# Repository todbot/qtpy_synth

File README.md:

# qtpy_synth

A simple [QTPy RP2040](https://learn.adafruit.com/adafruit-qt-py-2040/overview)-based
synth to experiment with [`synthio`](https://github.com/todbot/circuitpython-synthio-tricks).

### Features
 - Mono audio output circuit, converting PWM to audio, as per [RP2040 design guidelines](https://datasheets.raspberrypi.com/rp2040/hardware-design-with-rp2040.pdf#page=24)
 - Optoisolated MIDI Input via [MIDI TRS-A 3.5mm jack](https://www.perfectcircuit.com/make-noise-0-coast-midi-cable.html)
 - Two pots for controlling parameters
 - One switch for controlling parameters
 - Four capsense touch buttons for synth triggering
 - USB MIDI in/out of course too

### Software
Some programs written specifically for this board:

- [hwtest](./circuitpython/hwtest/code.py) - test out the hardware with a simple synth

- [simpletouchsynth](./circuitpython/simpletouchsynth) - play with filters using touch sensors. Uses intial cut at a "qtpy_synth" hardware library.

- [dronesynth](./circuitpython/dronesynth) - 8-oscillator drone synth

- [wavesynth](./circuitpython/wavesynth) - larger general two-osc synth that can also do wave-mixing and wavetables. Has many rough edges but can sound great!
  - early video demo:
  
    ]
  - another video demo:
  
    ]

#### See also:
- https://github.com/todbot/circuitpython-synthio-tricks
  - Contains [many other synthio examples](https://github.com/todbot/circuitpython-synthio-tricks/tree/main/examples) that can work with this synth with minimal changes

### Building it

The [Tindie version is a partially-assembled PCB](https://www.tindie.com/products/todbot/qtpy_synth/). 

The completely assembled SMD sections of the board are:

* audio output circuit
* TRS MIDI input circuit

The parts you need to add are:

* [QTPy RP2040](https://www.adafruit.com/product/4900)
* 0.91" [I2C OLED display](https://amzn.to/3KDmy73) (w/ pins in Gnd/Vcc/SCL/SDA order)
* Two 10k potentiometers, 9mm  ([example pots](https://amzn.to/3DYYJm5)) and [knobs](https://amzn.to/3QAkSyR)
* One tact switch, 6mm ([example switch](https://amzn.to/47nJaSN))
* Headers and sockets to mount QTPy & display, to taste
  * [This male & female header kit looks pretty good](https://amzn.to/3qqbtiO),
    as I prefer to put female headers on the PCB and male headers on the QTPy and OLED display.
    You may need to trim down your headers to be the right size.
* Feet. I like M2.5 nylon standoffs  (e.g. [M2.5 standoff asst kit](https://amzn.to/45qVjFb))
  but feel free to do what you like, including making an enclosure!
* Or [3d-print a simple case](https://www.printables.com/model/757087-case-for-qtpy_synth-circuitpython-synthesizer) for it! I also like these [3d-printed knobs](https://www.thingiverse.com/thing:5759656)

### Pins used

The board uses all of the QTPy RP2040 pins:

* `board.A0` - left knob
* `board.A1` - right knob
* `board.TX` - middle button
* `board.RX` - TRS UART MIDI in
* `board.MOSI` - PWM Audio Out
* `board.SCL` & `board.SDA` - I2C bus for OLED display
* `board.A3`, `board.A2`, `board.MISO`, `board.SCK`,  -- touch pads 1,2,3,4

For more details see [`hwtest/code.py`](https://github.com/todbot/qtpy_synth/tree/main/circuitpython/hwtest/code.py).

### Schematic

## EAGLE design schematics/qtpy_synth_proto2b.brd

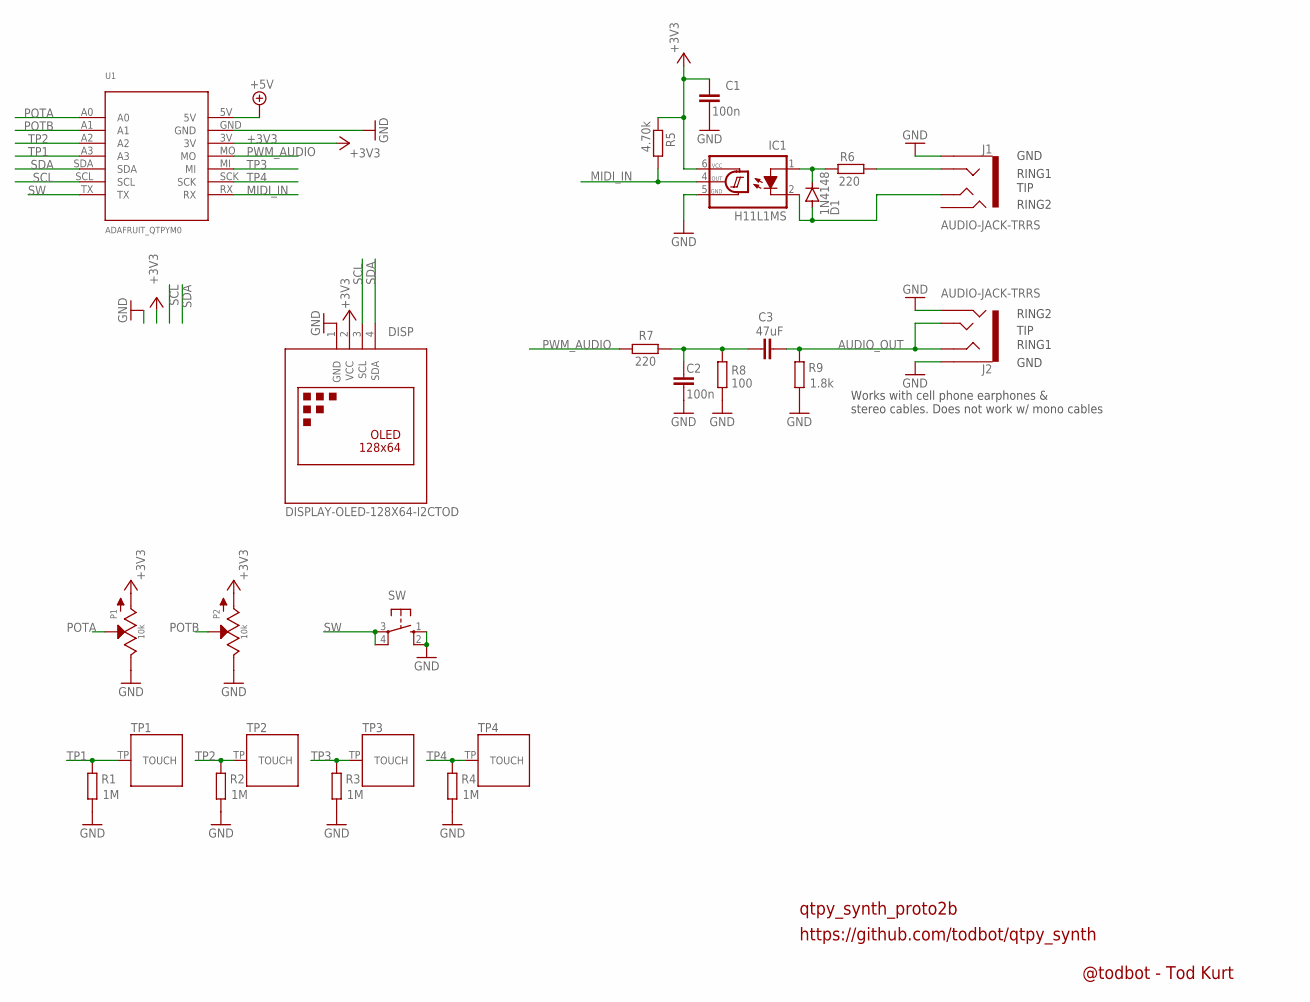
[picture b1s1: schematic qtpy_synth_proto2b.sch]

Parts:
C1, C2: 100n; C0805
C3: 47uF; C0805
D1: 1N4148; SOD123
DISP: DISPLAY-OLED-128X64-I2CTOD; DISPLAY-OLED-128X64-I2C-TOD
IC1: H11L1MS; DIL6-SMD; MPN2 H11L1S; LCSC C78589
J1: AUDIO-JACK-TRRS; PJ-320D_SPARKFUN
J2: AUDIO-JACK-TRRS; PJ-320D_SPARKFUN; LCSC C431535
P1, P2: 10k; OG-POTS_ALPS_POT_VERTICAL_WITHBIGKNOB
R1, R2, R3, R4: 1M; R0805
R5: 4.70k; R0805
R6, R7: 220; R0805
R8: 100; R0805
R9: 1.8k; R0805
SW: 10-XX; B3F-10XX
TP1, TP2, TP3, TP4: TOUCHPADA; TOUCHPADA_0.5IN
U1: ADAFRUIT_QTPYM0; ADAFRUIT_QTPY_M0

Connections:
+3V3: C1.1, DISP.2 (VCC), IC1.6 (VCC), P1.P$3 (A), P2.P$3 (A), R5.1, U1.3V
+5V: U1.5V
AUDIO_OUT: C3.2, J2.RING1, J2.TIP, R9.1
GND: C1.2, C2.2, DISP.1 (GND), IC1.5 (GND), J1.EARTH, J2.EARTH, J2.RING2, P1.P$1 (E), P2.P$1 (E), R1.2, R2.2, R3.2, R4.2, R8.1, R9.2, SW.1 (S), SW.2 (S1), U1.GND
MIDI_IN: IC1.4 (OUT), R5.2, U1.RX
unnamed: J1.RING1, R6.2
unnamed: D1.C, IC1.1 (A), R6.1
unnamed: D1.A, IC1.2 (C), J1.TIP
unnamed: C2.1, C3.1, R7.1, R8.2
POTA: P1.P$2 (S), U1.A0
POTB: P2.P$2 (S), U1.A1
PWM_AUDIO: R7.2, U1.MO
SCL: DISP.3 (SCL), U1.SCL
SDA: DISP.4 (SDA), U1.SDA
SW: SW.3, SW.4 (P1), U1.TX
TP1: R1.1, TP1.TP, U1.A3
TP2: R2.1, TP2.TP, U1.A2
TP3: R3.1, TP3.TP, U1.MI
TP4: R4.1, TP4.TP, U1.SCK

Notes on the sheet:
qtpy_synth_proto2b
https://github.com/todbot/qtpy_synth
RING2
RING1
GND
TIP
Works with cell phone earphones & stereo cables. Does not work w/ mono cables
@todbot - Tod Kurt

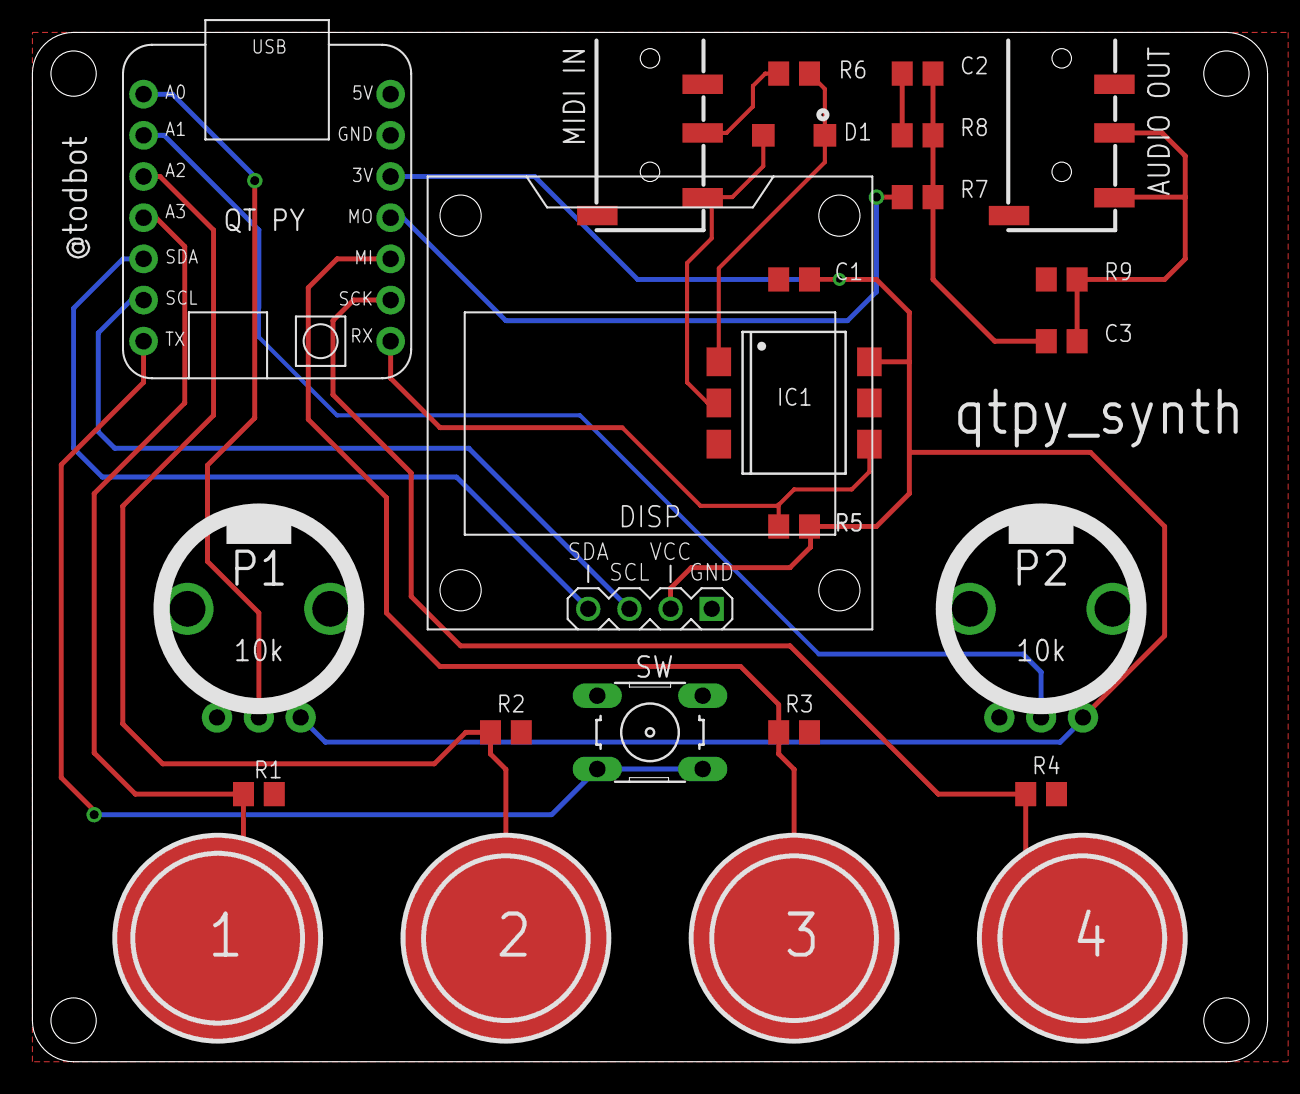
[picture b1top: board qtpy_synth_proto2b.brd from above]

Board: 2 copper layers, 76.2 x 63.5 mm, 25 parts (0 on the bottom side), 18 nets.

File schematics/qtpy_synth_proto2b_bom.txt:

Qty	Value	Device	Package	Parts	Description	LCSC	MF MPN
1		10-XX	B3F-10XX	SW	OMRON SWITCH		B3F-1000
1	1.8k	R-EU_R0805	R0805	R9	"RESISTOR, European symbol"		
1	100	R-EU_R0805	R0805	R8	"RESISTOR, European symbol"		
2	100n	C-EUC0805	C0805	"C1, C2"	"CAPACITOR, European symbol"		
2	10k	POTZEPHPOT_BIGKNOB	OG-POTS_ALPS_POT_VERTICAL_WITHBIGKNOB	"P1, P2"			
4	1M	R-EU_R0805	R0805	"R1, R2, R3, R4"	"RESISTOR, European symbol"		
1	1N4148	DIODE-SOD123	SOD123	D1	DIODE		
2	220	R-EU_R0805	R0805	"R6, R7"	"RESISTOR, European symbol"		
1	4.70k	R-EU_R0805	R0805	R5	"RESISTOR, European symbol"		
1	47uF	C-EUC0805	C0805	C3	"CAPACITOR, European symbol"		
1	ADAFRUIT_QTPYM0	ADAFRUIT_QTPYM0	ADAFRUIT_QTPY_M0	U1			
2	AUDIO-JACK-TRRS	AUDIO-JACK-TRRS	PJ-320D_SPARKFUN	"J1, J2"		C431535	PJ-320D
1	DISPLAY-OLED-128X64-I2CTOD	DISPLAY-OLED-128X64-I2CTOD	DISPLAY-OLED-128X64-I2C-TOD	DISP	128x64 Dot Matrix OLED Module	based on SSD1306 chip	
1	H11L1MS	H11L1MS	DIL6-SMD	IC1	6-Pin DIP Optocoupler	C78589

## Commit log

2023-06-28 first
2023-06-28 fix name, add hwtest
2023-07-12 sync up
2023-07-12 hwtest5 with synthio_instrument sorta working
2023-07-13 some docs
2023-07-17 more progress on synthio_instrument
2023-07-23 wavetable synth working ish
2023-07-23 waveetable: getting out-of-memory when switching patches when in_memory=True, so just default to False for now
2023-07-24 wavetable, now with multi wavetable
2023-07-28 gerbers for proto2b
2023-07-28 added proto2b bom
2023-07-29 pdf of proto2b sch
2023-07-29 add link to synthio-tricks
2023-08-03 promote hwtest2 as initial hwtest code
2023-08-04 fix oled holes
2023-08-04 promote some test scripts to "real" programs I guess
2023-08-04 trying to figure out patch management
2023-08-04 refactor wavesynth code, cleaning up synthio_instrument for potential publish as standalone library
2023-08-04 added 4th config line to display, not working right yet
2023-08-04 cleanup hwtest4 to turn it into simpletouchsynth
2023-08-04 cleanup simpletouchsynth
2023-08-04 cleanup
2023-08-05 add midi to simpletouchsynth because why not
2023-08-05 simpletouchsynth cleanup
2023-08-05 sync up qtpy_synth.py, update it for simpletouchsynth
2023-08-05 cleanup proto2b pcb before fab submit
2023-08-05 simpletouchsynth add hellotext
2023-08-05 cleanup gerbers
2023-08-10 add links to video demos
2023-08-10 add to readme
2023-08-11 fine I will use displayio for hwtest
2023-08-11 link to trs-a cable and hwtest script
2023-08-15 cleanup hwtest/code.py
2023-08-15 more readme
2023-08-15 explicitly note which pins are used in readme
2024-02-07 update hwtest to use smolmidi and make noise on midi receive
2024-02-07 clean up code so reuse can occur easier, move to winterbloom_smolmidi
2024-02-07 more reorg
2024-02-07 fix typo
2024-02-09 code cleanup
2024-02-09 added 3d case
2024-02-09 cleanup wavesynth
2024-02-09 fix youtube links
2024-02-10 hwtest cleanup, after doing some USB MIDI timing and cpu overclocking tests
2024-04-26 code layout rearrange and dronesynth start
2024-04-27 better dronesynth version
2024-04-27 dronesynth now has display of sorts
2024-04-27 dronesynth fixes
2024-04-28 more dronesynth
2024-04-28 drone drone drone
